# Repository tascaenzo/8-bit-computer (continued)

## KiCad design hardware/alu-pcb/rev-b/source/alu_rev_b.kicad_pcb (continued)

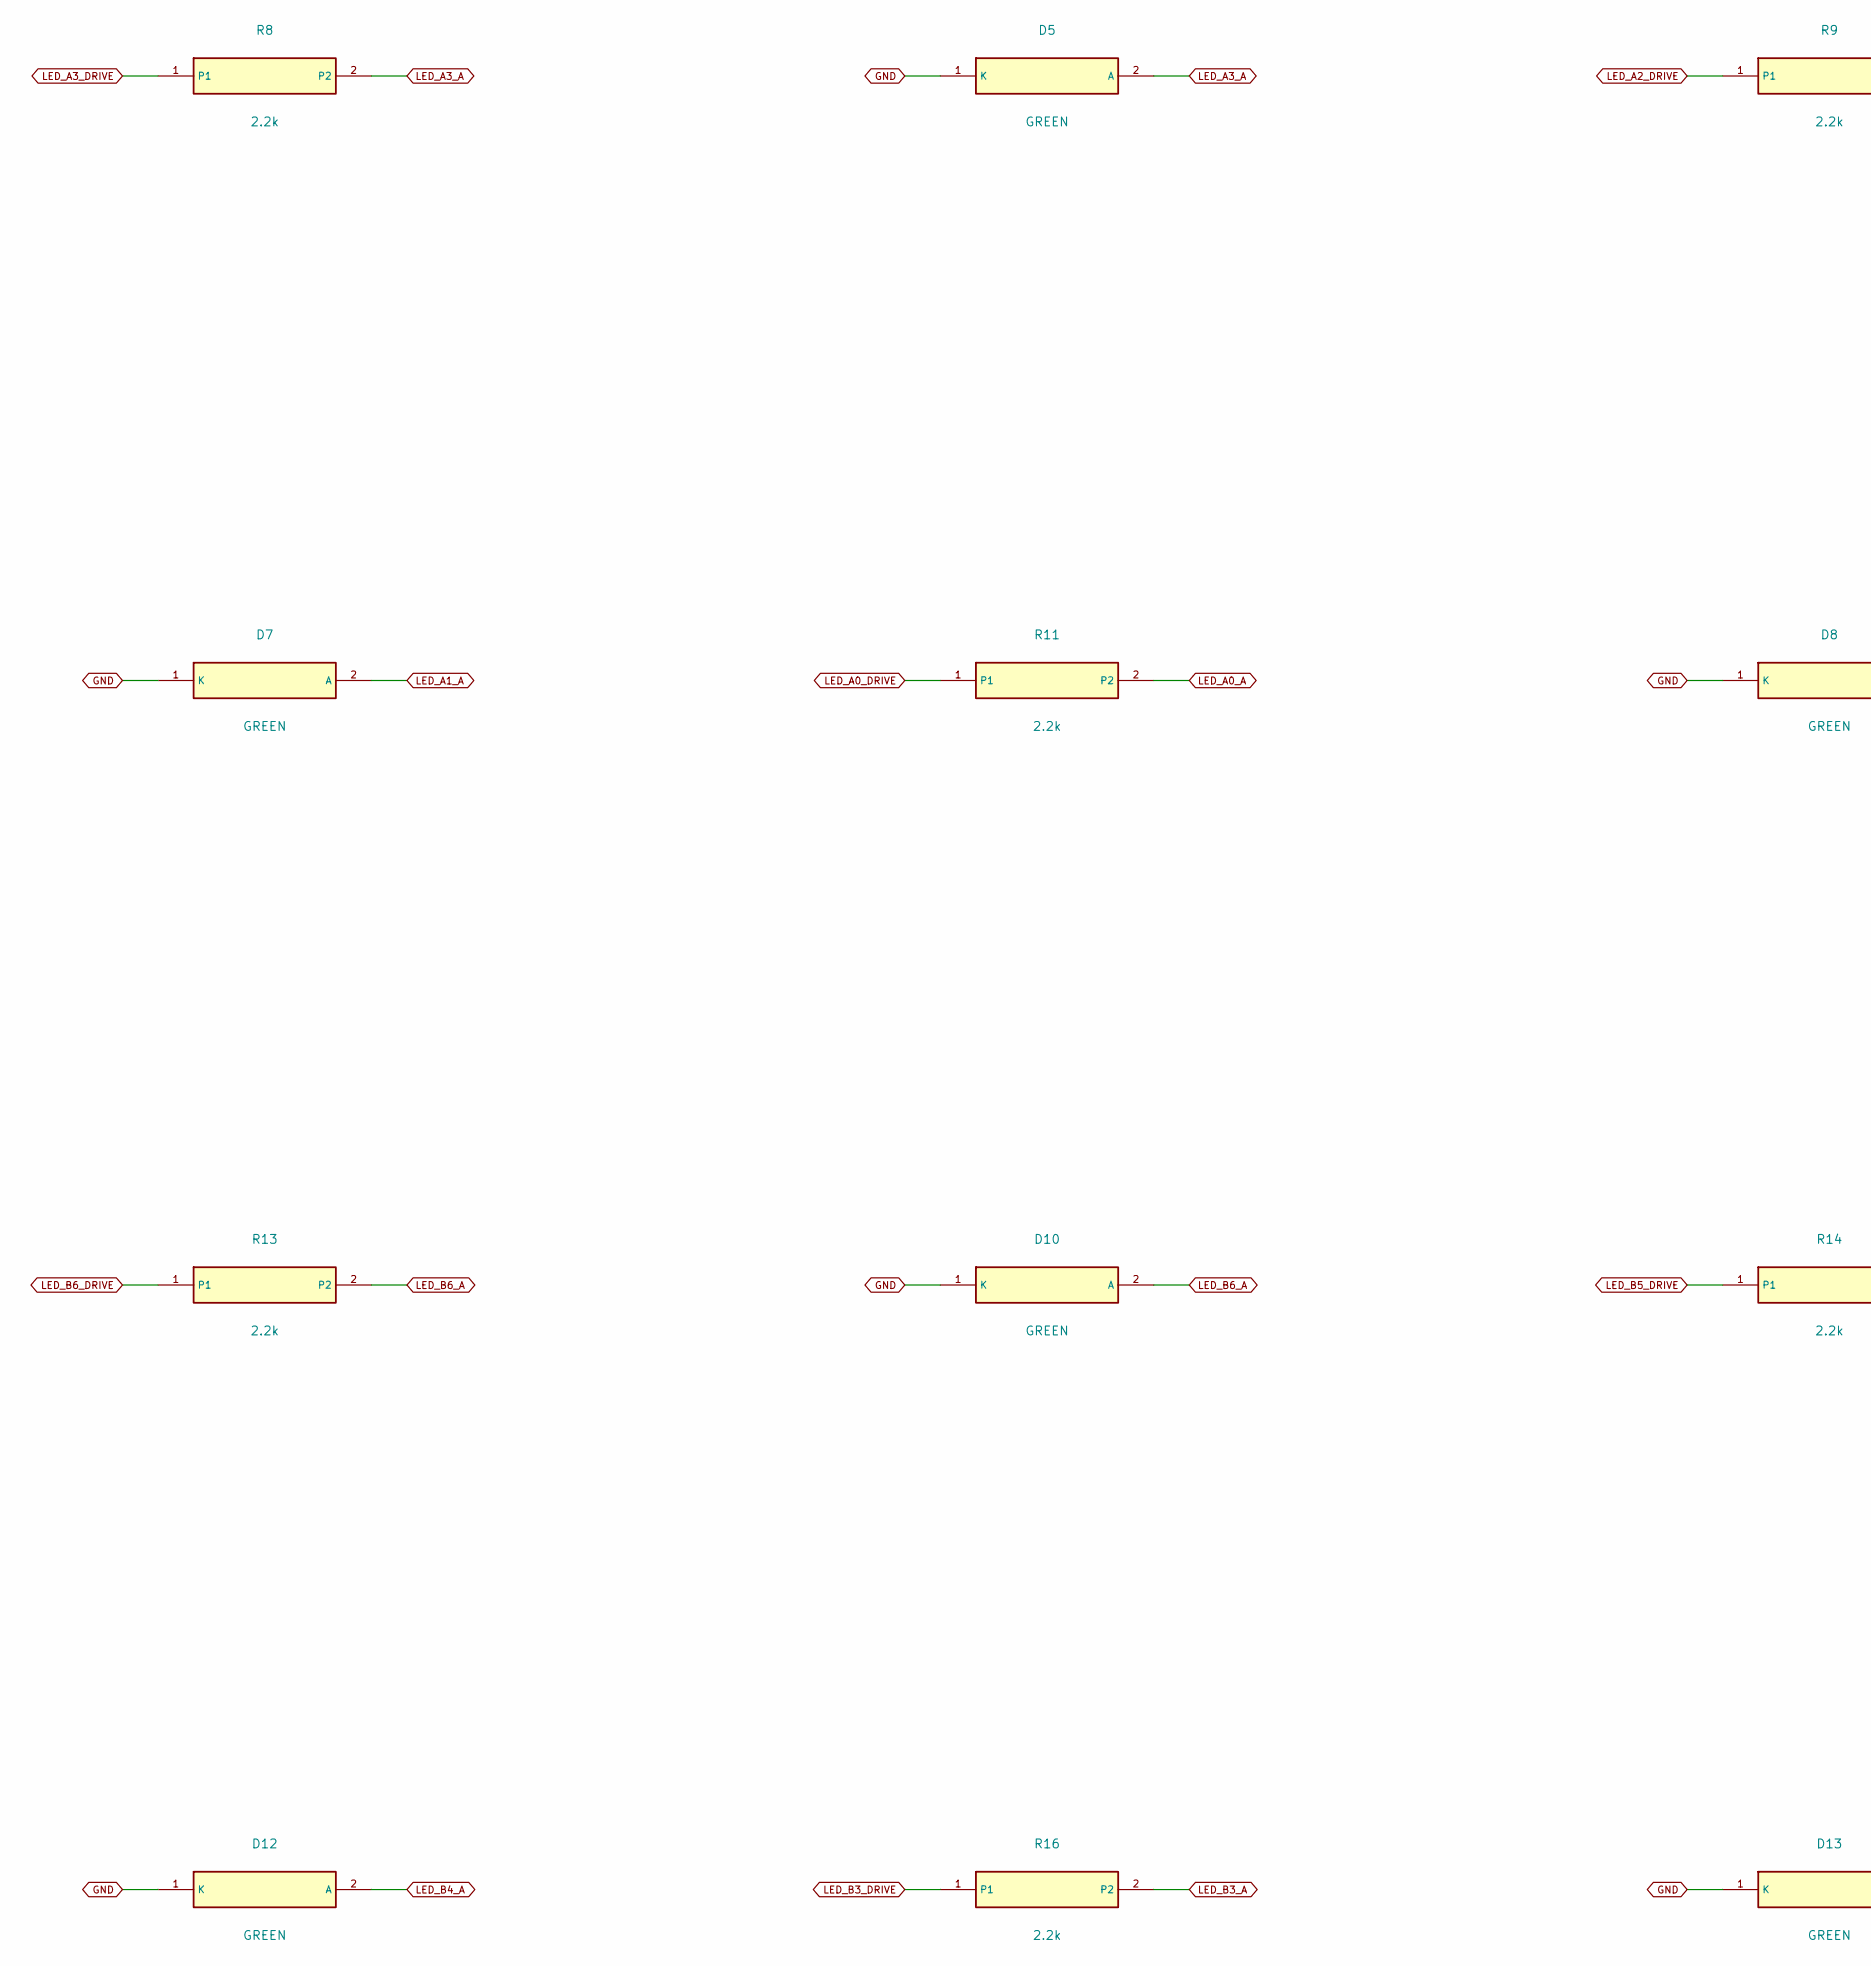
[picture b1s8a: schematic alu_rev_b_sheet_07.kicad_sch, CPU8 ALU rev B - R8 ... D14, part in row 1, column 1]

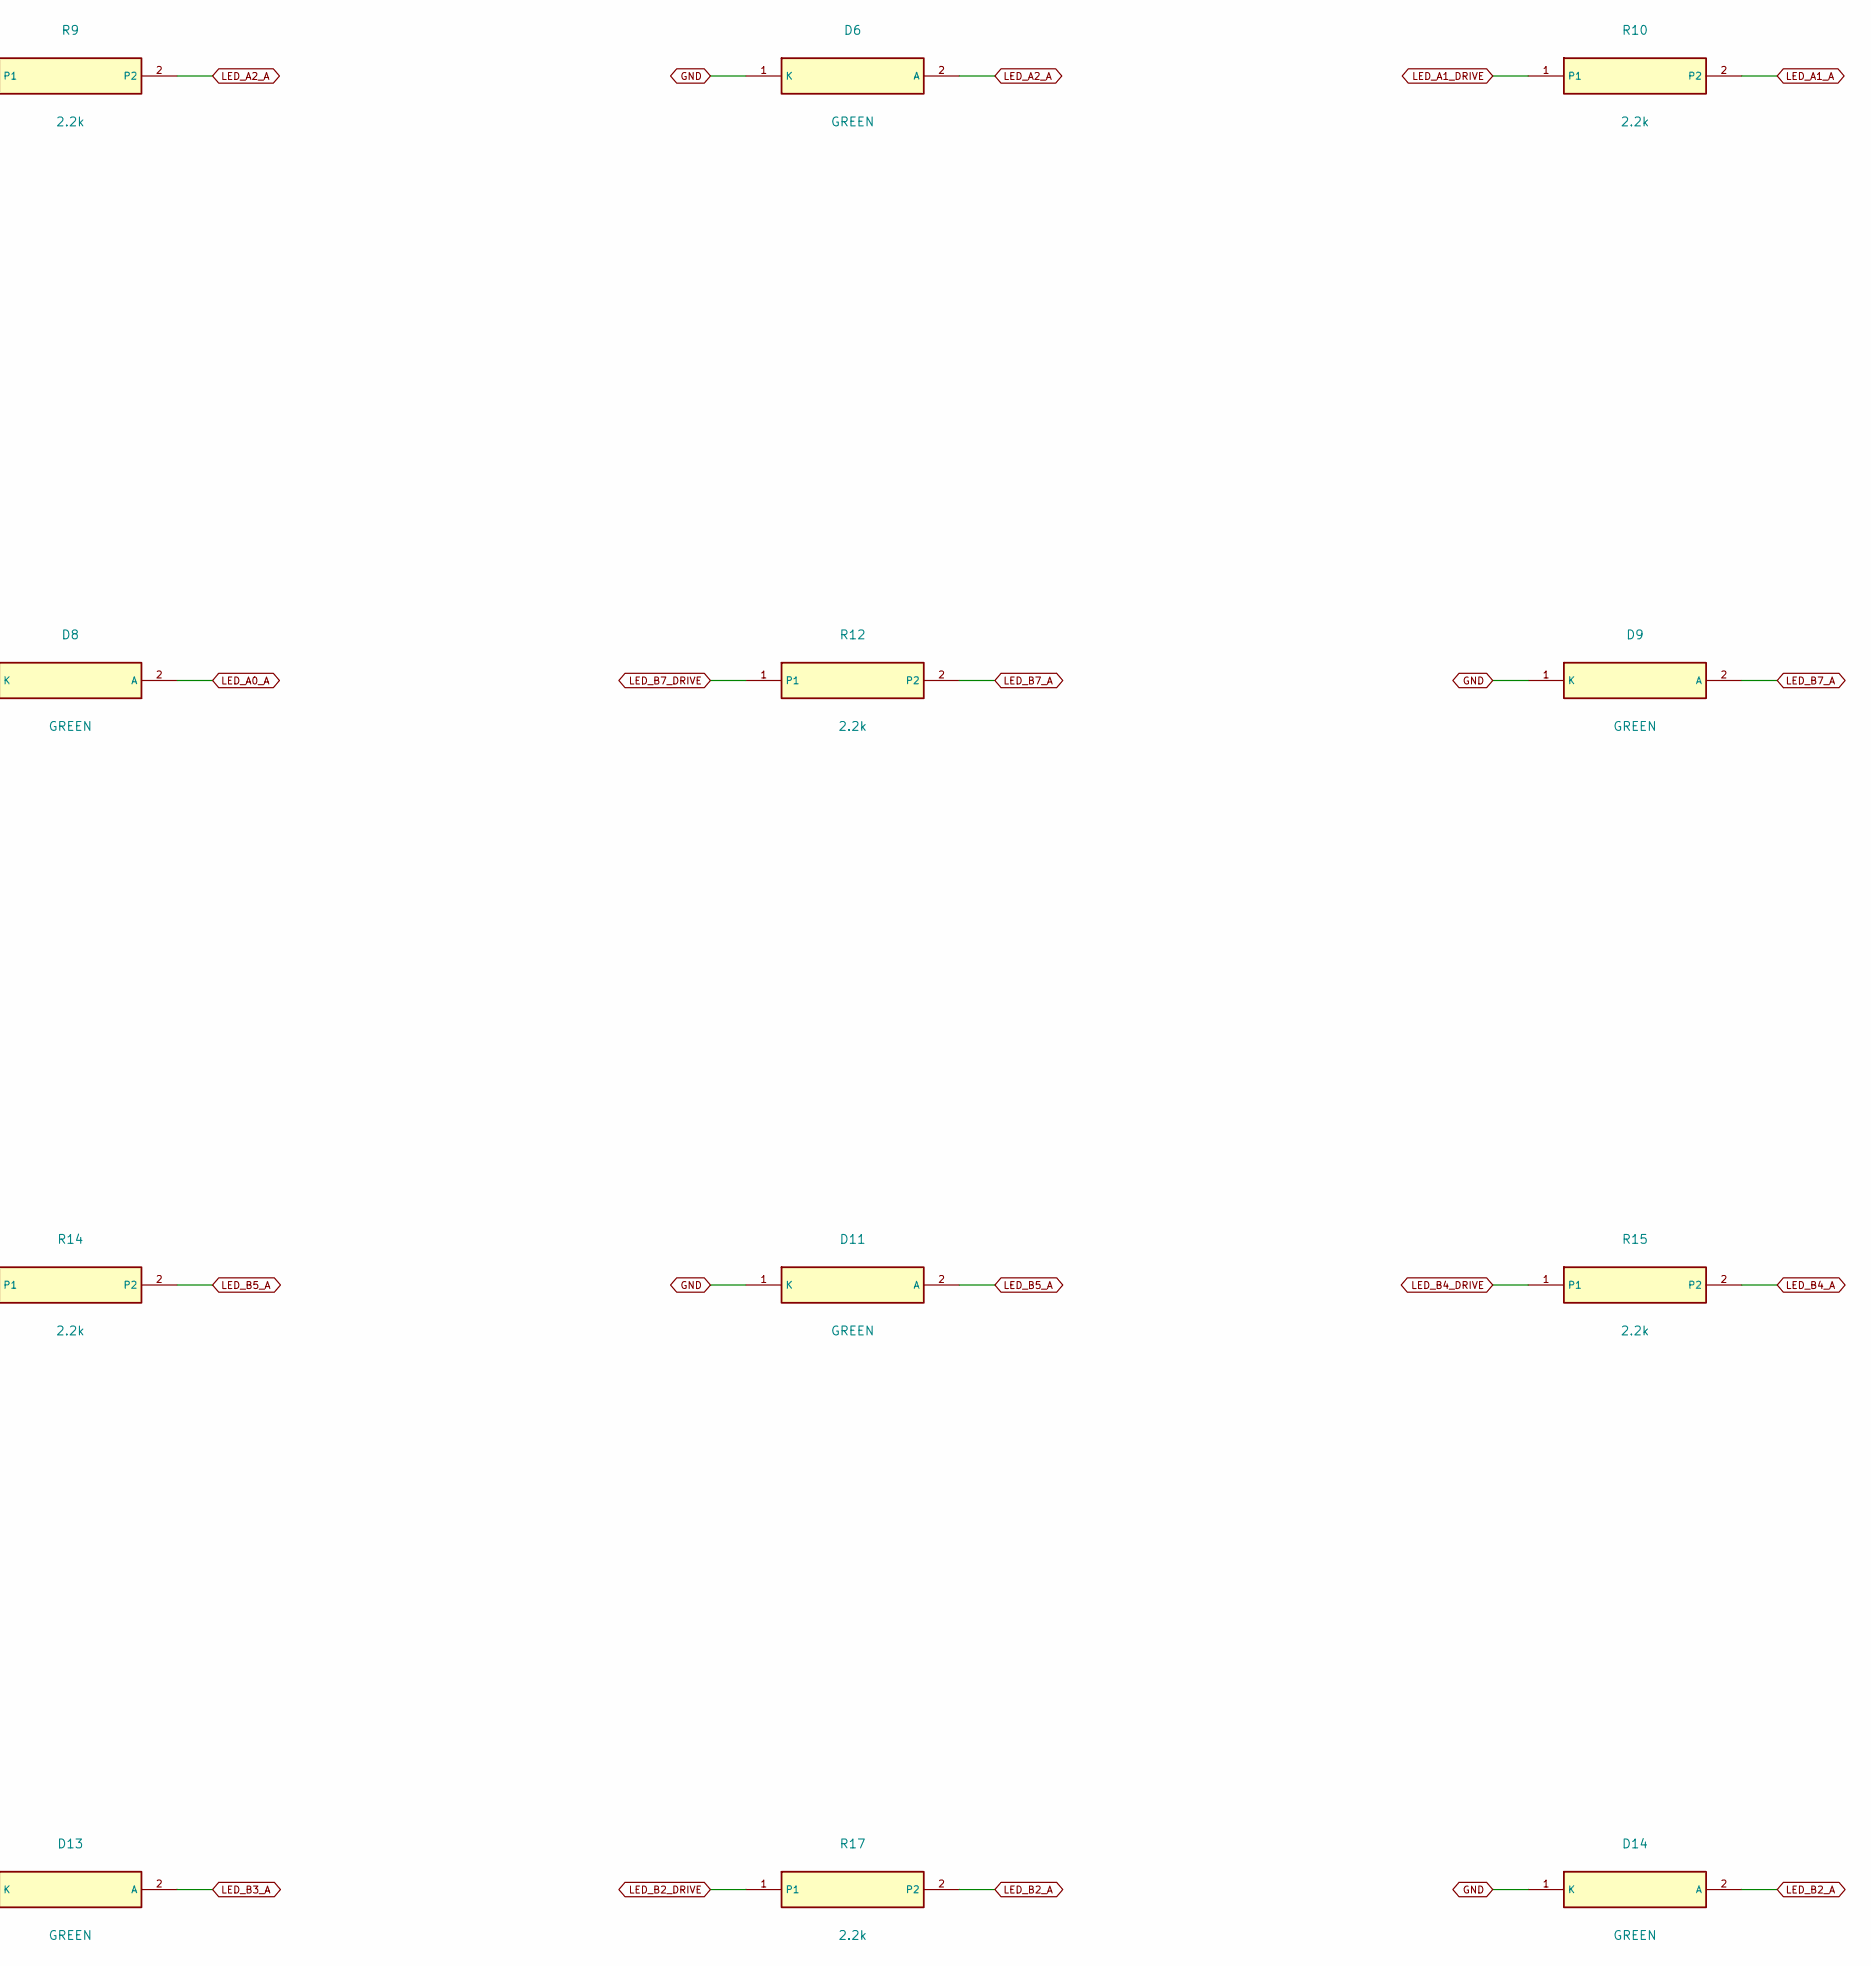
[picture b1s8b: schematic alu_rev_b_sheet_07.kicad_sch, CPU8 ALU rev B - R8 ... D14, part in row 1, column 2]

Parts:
D5, D6, D7, D8, D9, D10, D11, D12, D13, D14: GREEN; LED_D3.0mm_P2.54mm
R8, R9, R10, R11, R12, R13, R14, R15, R16, R17: 2.2k; R_Axial_P7.62mm

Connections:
GND: D5.1 (K), D6.1 (K), D7.1 (K), D8.1 (K), D9.1 (K), D10.1 (K), D11.1 (K), D12.1 (K), D13.1 (K), D14.1 (K); also elsewhere on the board
LED_A0_A: D8.2 (A), R11.2
LED_A0_DRIVE: R11.1; also elsewhere on the board
LED_A1_A: D7.2 (A), R10.2
LED_A1_DRIVE: R10.1; also elsewhere on the board
LED_A2_A: D6.2 (A), R9.2
LED_A2_DRIVE: R9.1; also elsewhere on the board
LED_A3_A: D5.2 (A), R8.2
LED_A3_DRIVE: R8.1; also elsewhere on the board
LED_B2_A: D14.2 (A), R17.2
LED_B2_DRIVE: R17.1; also elsewhere on the board
LED_B3_A: D13.2 (A), R16.2
LED_B3_DRIVE: R16.1; also elsewhere on the board
LED_B4_A: D12.2 (A), R15.2
LED_B4_DRIVE: R15.1; also elsewhere on the board
LED_B5_A: D11.2 (A), R14.2
LED_B5_DRIVE: R14.1; also elsewhere on the board
LED_B6_A: D10.2 (A), R13.2
LED_B6_DRIVE: R13.1; also elsewhere on the board
LED_B7_A: D9.2 (A), R12.2
LED_B7_DRIVE: R12.1; also elsewhere on the board

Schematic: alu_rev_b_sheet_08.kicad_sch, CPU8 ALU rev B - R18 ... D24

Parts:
D15, D16: GREEN; LED_D3.0mm_P2.54mm
D17, D18, D19, D20: YELLOW; LED_D3.0mm_P2.54mm
D21, D22, D23, D24: BLUE; LED_D3.0mm_P2.54mm
R18, R19, R20, R21, R22, R23, R24, R25, R26, R27: 2.2k; R_Axial_P7.62mm

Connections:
+5V: R24.1, R25.1, R26.1, R27.1; also elsewhere on the board
GND: D15.1 (K), D16.1 (K), D17.1 (K), D18.1 (K), D19.1 (K), D20.1 (K); also elsewhere on the board
LED_AND_A: D21.2 (A), R24.2
LED_B0_A: D16.2 (A), R19.2
LED_B0_DRIVE: R19.1; also elsewhere on the board
LED_B1_A: D15.2 (A), R18.2
LED_B1_DRIVE: R18.1; also elsewhere on the board
LED_C_A: D17.2 (A), R20.2
LED_C_DRIVE: R20.1; also elsewhere on the board
LED_NOR_A: D24.2 (A), R27.2
LED_N_A: D19.2 (A), R22.2
LED_N_DRIVE: R22.1; also elsewhere on the board
LED_OR_A: D22.2 (A), R25.2
LED_O_A: D20.2 (A), R23.2
LED_O_DRIVE: R23.1; also elsewhere on the board
LED_XOR_A: D23.2 (A), R26.2
LED_Z_A: D18.2 (A), R21.2
LED_Z_DRIVE: R21.1; also elsewhere on the board
OP_AND_n: D21.1 (K); also elsewhere on the board
OP_NOR_n: D24.1 (K); also elsewhere on the board
OP_OR_n: D22.1 (K); also elsewhere on the board
OP_XOR_n: D23.1 (K); also elsewhere on the board

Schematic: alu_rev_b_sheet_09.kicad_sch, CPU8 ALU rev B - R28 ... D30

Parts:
D25, D26, D27, D28, D29, D30: BLUE; LED_D3.0mm_P2.54mm
R28, R29, R30, R31, R32, R33: 2.2k; R_Axial_P7.62mm

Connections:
+5V: R28.1, R29.1, R30.1, R31.1, R32.1, R33.1; also elsewhere on the board
LED_ADD_A: D28.2 (A), R31.2
LED_CMP_A: D30.2 (A), R33.2
LED_NAND_A: D25.2 (A), R28.2
LED_NOT_A: D27.2 (A), R30.2
LED_SUB_A: D29.2 (A), R32.2
LED_XNOR_A: D26.2 (A), R29.2
OP_ADD_n: D28.1 (K); also elsewhere on the board
OP_CMP_n: D30.1 (K); also elsewhere on the board
OP_NAND_n: D25.1 (K); also elsewhere on the board
OP_NOT_n: D27.1 (K); also elsewhere on the board
OP_SUB_n: D29.1 (K); also elsewhere on the board
OP_XNOR_n: D26.1 (K); also elsewhere on the board

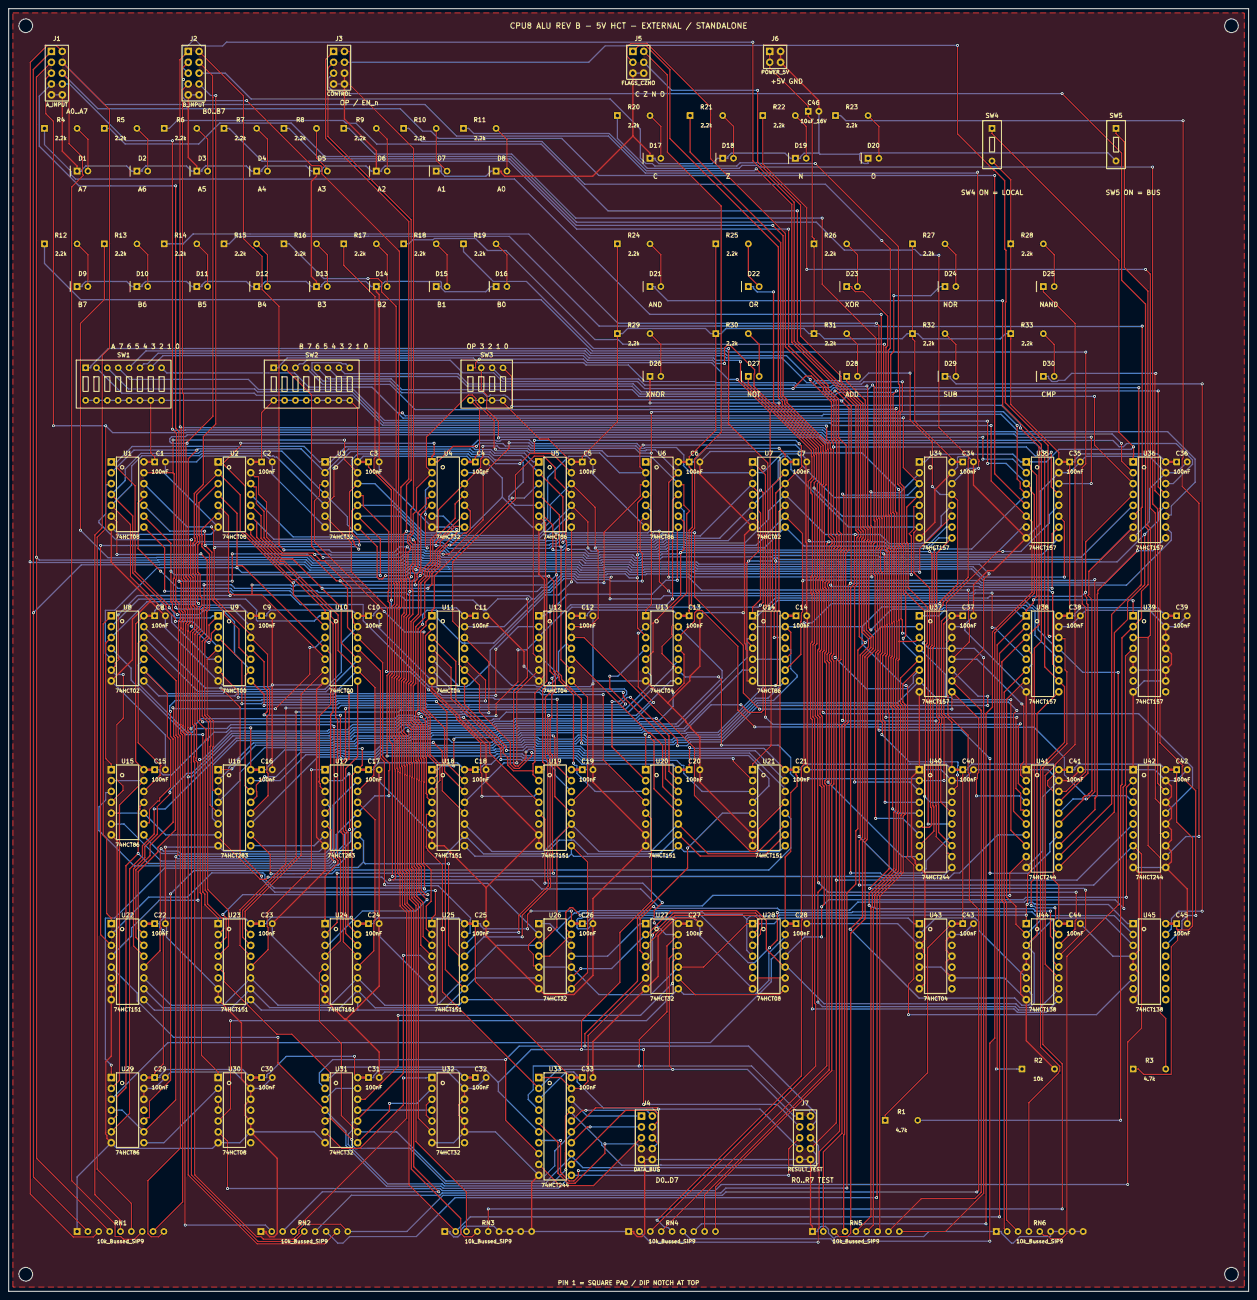
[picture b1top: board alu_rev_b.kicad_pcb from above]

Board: 2 copper layers, 290.0 x 300.0 mm, 172 parts (0 on the bottom side), 242 nets.

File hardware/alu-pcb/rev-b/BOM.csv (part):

Reference,Value,Footprint,Purpose,Part_or_requirement,Mounting_specification
U1,74HCT08,DIP-14_W7.62mm,AND,74HCT08 compatible pinout,5V HCT; PDIP-14; rows 7.62mm; optional socket
U2,74HCT08,DIP-14_W7.62mm,AND,74HCT08 compatible pinout,5V HCT; PDIP-14; rows 7.62mm; optional socket
U3,74HCT32,DIP-14_W7.62mm,OR,74HCT32 compatible pinout,5V HCT; PDIP-14; rows 7.62mm; optional socket
U4,74HCT32,DIP-14_W7.62mm,OR,74HCT32 compatible pinout,5V HCT; PDIP-14; rows 7.62mm; optional socket
U5,74HCT86,DIP-14_W7.62mm,XOR,74HCT86 compatible pinout,5V HCT; PDIP-14; rows 7.62mm; optional socket
U6,74HCT86,DIP-14_W7.62mm,XOR,74HCT86 compatible pinout,5V HCT; PDIP-14; rows 7.62mm; optional socket
U7,74HCT02,DIP-14_W7.62mm,NOR,74HCT02 compatible pinout,5V HCT; PDIP-14; rows 7.62mm; optional socket
U8,74HCT02,DIP-14_W7.62mm,NOR,74HCT02 compatible pinout,5V HCT; PDIP-14; rows 7.62mm; optional socket
U9,74HCT00,DIP-14_W7.62mm,NAND,74HCT00 compatible pinout,5V HCT; PDIP-14; rows 7.62mm; optional socket
U10,74HCT00,DIP-14_W7.62mm,NAND,74HCT00 compatible pinout,5V HCT; PDIP-14; rows 7.62mm; optional socket
U11,74HCT04,DIP-14_W7.62mm,XNOR / NOT,74HCT04 compatible pinout,5V HCT; PDIP-14; rows 7.62mm; optional socket
U12,74HCT04,DIP-14_W7.62mm,XNOR / NOT,74HCT04 compatible pinout,5V HCT; PDIP-14; rows 7.62mm; optional socket
U13,74HCT04,DIP-14_W7.62mm,XNOR / NOT,74HCT04 compatible pinout,5V HCT; PDIP-14; rows 7.62mm; optional socket
U14,74HCT86,DIP-14_W7.62mm,B complement,74HCT86 compatible pinout,5V HCT; PDIP-14; rows 7.62mm; optional socket
U15,74HCT86,DIP-14_W7.62mm,B complement,74HCT86 compatible pinout,5V HCT; PDIP-14; rows 7.62mm; optional socket
U16,74HCT283,DIP-16_W7.62mm,Adder bits 0..3,CD74HCT283E,5V HCT; PDIP-16; rows 7.62mm; optional socket
U17,74HCT283,DIP-16_W7.62mm,Adder bits 4..7,CD74HCT283E,5V HCT; PDIP-16; rows 7.62mm; optional socket
U18,74HCT151,DIP-16_W7.62mm,Result select bit 0,CD74HCT151E,5V HCT; PDIP-16; rows 7.62mm; optional socket
U19,74HCT151,DIP-16_W7.62mm,Result select bit 1,CD74HCT151E,5V HCT; PDIP-16; rows 7.62mm; optional socket
U20,74HCT151,DIP-16_W7.62mm,Result select bit 2,CD74HCT151E,5V HCT; PDIP-16; rows 7.62mm; optional socket
U21,74HCT151,DIP-16_W7.62mm,Result select bit 3,CD74HCT151E,5V HCT; PDIP-16; rows 7.62mm; optional socket
U22,74HCT151,DIP-16_W7.62mm,Result select bit 4,CD74HCT151E,5V HCT; PDIP-16; rows 7.62mm; optional socket
U23,74HCT151,DIP-16_W7.62mm,Result select bit 5,CD74HCT151E,5V HCT; PDIP-16; rows 7.62mm; optional socket
U24,74HCT151,DIP-16_W7.62mm,Result select bit 6,CD74HCT151E,5V HCT; PDIP-16; rows 7.62mm; optional socket
U25,74HCT151,DIP-16_W7.62mm,Result select bit 7,CD74HCT151E,5V HCT; PDIP-16; rows 7.62mm; optional socket
U26,74HCT32,DIP-14_W7.62mm,Opcode / output control,74HCT32 compatible pinout,5V HCT; PDIP-14; rows 7.62mm; optional socket
U27,74HCT32,DIP-14_W7.62mm,Opcode / output control,74HCT32 compatible pinout,5V HCT; PDIP-14; rows 7.62mm; optional socket
U28,74HCT08,DIP-14_W7.62mm,Opcode / output control,74HCT08 compatible pinout,5V HCT; PDIP-14; rows 7.62mm; optional socket
U29,74HCT86,DIP-14_W7.62mm,Carry / overflow,74HCT86 compatible pinout,5V HCT; PDIP-14; rows 7.62mm; optional socket
U30,74HCT08,DIP-14_W7.62mm,Carry / overflow,74HCT08 compatible pinout,5V HCT; PDIP-14; rows 7.62mm; optional socket
U31,74HCT32,DIP-14_W7.62mm,Zero flag,74HCT32 compatible pinout,5V HCT; PDIP-14; rows 7.62mm; optional socket
U32,74HCT32,DIP-14_W7.62mm,Zero flag,74HCT32 compatible pinout,5V HCT; PDIP-14; rows 7.62mm; optional socket
U33,74HCT244,DIP-20_W7.62mm,Shared bus output,SN74HCT244N,5V HCT; PDIP-20; rows 7.62mm; optional socket
U34,74HCT157,DIP-16_W7.62mm,External / standalone input selection,SN74HCT157N,5V HCT; PDIP-16; rows 7.62mm; optional socket
U35,74HCT157,DIP-16_W7.62mm,External / standalone input selection,SN74HCT157N,5V HCT; PDIP-16; rows 7.62mm; optional socket
U36,74HCT157,DIP-16_W7.62mm,External / standalone input selection,SN74HCT157N,5V HCT; PDIP-16; rows 7.62mm; optional socket
U37,74HCT157,DIP-16_W7.62mm,External / standalone input selection,SN74HCT157N,5V HCT; PDIP-16; rows 7.62mm; optional socket
U38,74HCT157,DIP-16_W7.62mm,External / standalone input selection,SN74HCT157N,5V HCT; PDIP-16; rows 7.62mm; optional socket
U39,74HCT157,DIP-16_W7.62mm,External / standalone input selection,SN74HCT157N,5V HCT; PDIP-16; rows 7.62mm; optional socket
U40,74HCT244,DIP-20_W7.62mm,Operand / flag LED driver,SN74HCT244N,5V HCT; PDIP-20; rows 7.62mm; optional socket
U41,74HCT244,DIP-20_W7.62mm,Operand / flag LED driver,SN74HCT244N,5V HCT; PDIP-20; rows 7.62mm; optional socket
U42,74HCT244,DIP-20_W7.62mm,Operand / flag LED driver,SN74HCT244N,5V HCT; PDIP-20; rows 7.62mm; optional socket
U43,74HCT04,DIP-14_W7.62mm,Opcode LED decoder enable,74HCT04 compatible pinout,5V HCT; PDIP-14; rows 7.62mm; optional socket
U44,74HCT138,DIP-16_W7.62mm,Operation LED decoder,SN74HCT138N,5V HCT; PDIP-16; rows 7.62mm; optional socket
U45,74HCT138,DIP-16_W7.62mm,Operation LED decoder,SN74HCT138N,5V HCT; PDIP-16; rows 7.62mm; optional socket
C1,100nF,C_Disc_P2.50mm,Local bypass,100nF 25V ceramic,Pitch 2.50mm; body max 4x3mm; nonpolarized
C2,100nF,C_Disc_P2.50mm,Local bypass,100nF 25V ceramic,Pitch 2.50mm; body max 4x3mm; nonpolarized
C3,100nF,C_Disc_P2.50mm,Local bypass,100nF 25V ceramic,Pitch 2.50mm; body max 4x3mm; nonpolarized
C4,100nF,C_Disc_P2.50mm,Local bypass,100nF 25V ceramic,Pitch 2.50mm; body max 4x3mm; nonpolarized
C5,100nF,C_Disc_P2.50mm,Local bypass,100nF 25V ceramic,Pitch 2.50mm; body max 4x3mm; nonpolarized
C6,100nF,C_Disc_P2.50mm,Local bypass,100nF 25V ceramic,Pitch 2.50mm; body max 4x3mm; nonpolarized
C7,100nF,C_Disc_P2.50mm,Local bypass,100nF 25V ceramic,Pitch 2.50mm; body max 4x3mm; nonpolarized
C8,100nF,C_Disc_P2.50mm,Local bypass,100nF 25V ceramic,Pitch 2.50mm; body max 4x3mm; nonpolarized
C9,100nF,C_Disc_P2.50mm,Local bypass,100nF 25V ceramic,Pitch 2.50mm; body max 4x3mm; nonpolarized
C10,100nF,C_Disc_P2.50mm,Local bypass,100nF 25V ceramic,Pitch 2.50mm; body max 4x3mm; nonpolarized
C11,100nF,C_Disc_P2.50mm,Local bypass,100nF 25V ceramic,Pitch 2.50mm; body max 4x3mm; nonpolarized
C12,100nF,C_Disc_P2.50mm,Local bypass,100nF 25V ceramic,Pitch 2.50mm; body max 4x3mm; nonpolarized
C13,100nF,C_Disc_P2.50mm,Local bypass,100nF 25V ceramic,Pitch 2.50mm; body max 4x3mm; nonpolarized
C14,100nF,C_Disc_P2.50mm,Local bypass,100nF 25V ceramic,Pitch 2.50mm; body max 4x3mm; nonpolarized
C15,100nF,C_Disc_P2.50mm,Local bypass,100nF 25V ceramic,Pitch 2.50mm; body max 4x3mm; nonpolarized
C16,100nF,C_Disc_P2.50mm,Local bypass,100nF 25V ceramic,Pitch 2.50mm; body max 4x3mm; nonpolarized
C17,100nF,C_Disc_P2.50mm,Local bypass,100nF 25V ceramic,Pitch 2.50mm; body max 4x3mm; nonpolarized
C18,100nF,C_Disc_P2.50mm,Local bypass,100nF 25V ceramic,Pitch 2.50mm; body max 4x3mm; nonpolarized
C19,100nF,C_Disc_P2.50mm,Local bypass,100nF 25V ceramic,Pitch 2.50mm; body max 4x3mm; nonpolarized
C20,100nF,C_Disc_P2.50mm,Local bypass,100nF 25V ceramic,Pitch 2.50mm; body max 4x3mm; nonpolarized
C21,100nF,C_Disc_P2.50mm,Local bypass,100nF 25V ceramic,Pitch 2.50mm; body max 4x3mm; nonpolarized
C22,100nF,C_Disc_P2.50mm,Local bypass,100nF 25V ceramic,Pitch 2.50mm; body max 4x3mm; nonpolarized
C23,100nF,C_Disc_P2.50mm,Local bypass,100nF 25V ceramic,Pitch 2.50mm; body max 4x3mm; nonpolarized
C24,100nF,C_Disc_P2.50mm,Local bypass,100nF 25V ceramic,Pitch 2.50mm; body max 4x3mm; nonpolarized
C25,100nF,C_Disc_P2.50mm,Local bypass,100nF 25V ceramic,Pitch 2.50mm; body max 4x3mm; nonpolarized
C26,100nF,C_Disc_P2.50mm,Local bypass,100nF 25V ceramic,Pitch 2.50mm; body max 4x3mm; nonpolarized
C27,100nF,C_Disc_P2.50mm,Local bypass,100nF 25V ceramic,Pitch 2.50mm; body max 4x3mm; nonpolarized
C28,100nF,C_Disc_P2.50mm,Local bypass,100nF 25V ceramic,Pitch 2.50mm; body max 4x3mm; nonpolarized
C29,100nF,C_Disc_P2.50mm,Local bypass,100nF 25V ceramic,Pitch 2.50mm; body max 4x3mm; nonpolarized
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
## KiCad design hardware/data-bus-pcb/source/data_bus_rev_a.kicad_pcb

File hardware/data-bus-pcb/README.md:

# CPU8 — bus dati a 8 bit, revisione A

Layout slim con LED compatti e switch del 7 ottobre 2026: **235 × 40 mm**, rispetto ai precedenti 180 × 60 mm.
Il 74HCT244 segue la fila degli otto connettori sul lato destro.
Serigrafia sul fronte: **Progettato da Enzo Tasca**. Questa versione usa la
revisione **A**, come richiesto, e sostituisce il precedente layout B.
Le piedinature elettriche rimangono compatibili con ALU J4/J6.

PCB da saldare con **otto porte bidirezionali** J1…J8, **otto LED D7…D0**,
un buffer per gli indicatori e una spia PWR. Tutte le porte sono collegate
in parallelo: qualunque porta può essere usata da un modulo che legge
oppure da un modulo che scrive. Il connettore dati è compatibile con
**J4 dell'ALU revisione A** del repository.

La scheda distribuisce dati e massa. L'alimentazione del monitor entra da
J9; il clock, i comandi LOAD e le abilitazioni delle uscite viaggiano
separatamente, dalla centralina ai rispettivi moduli.

## File consegnati

- `CPU8_DATA_BUS_REV_A_GERBER.zip`: da caricare sul servizio di produzione PCB.
- `CPU8_DATA_BUS_REV_A_PROJECT.zip`: sorgenti KiCad, librerie, schema, BOM e rapporti.
- `source/data_bus_rev_a.kicad_pro`: progetto da aprire in KiCad.
- `data_bus_rev_a_schematic.pdf`: schema elettrico, tre pagine.
- `data_bus_rev_a_preview.png`: anteprima della scheda nuda, senza modelli dei componenti.
- `data_bus_rev_a_layout.svg`: piste e serigrafia.
- `BOM.csv`: distinta con valori, package e dimensioni per il montaggio.
- `verification/`: controlli elettrici, di layout, di collegamento e integrità degli export.

Lo ZIP Gerber ordina una **scheda vuota**: i componenti e gli zoccoli vanno
acquistati e saldati separatamente. Non è stato effettuato alcun ordine.

## Piedinatura

Guardando il lato componenti con il titolo in alto, il pin 1 è la piazzola
quadrata in alto a sinistra. Tutti i connettori hanno due colonne a passo
2,54 mm: righe 1/2, 3/4, 5/6, ecc.

| Porta dati J1…J8 | Colonna sinistra | Colonna destra |
| --- | --- | --- |
| Riga 1 | Pin 1: D0 | Pin 2: D1 |
| Riga 2 | Pin 3: D2 | Pin 4: D3 |
| Riga 3 | Pin 5: D4 | Pin 6: D5 |
| Riga 4 | Pin 7: D6 | Pin 8: D7 |
| Riga 5 | Pin 9: GND | Pin 10: GND |

**Le porte dati non contengono +5 V.** Usare header maschi non schermati
2×5 e cavi con collegamento pin-a-pin. Non ruotare il connettore di 180°;
controllare i cavi con il tester prima dell'accensione.

| J9 POWER_5V | Colonna sinistra | Colonna destra |
| --- | --- | --- |
| Riga 1 | Pin 1: +5 V | Pin 2: GND |
| Riga 2 | Pin 3: +5 V | Pin 4: GND |

J9 è un header 2×2 con la stessa piedinatura di J6 dell'ALU. Alimentare
monitor e moduli da una sorgente comune a **5 V regolati** e collegare le
masse. I moduli ricevono +5 V dai loro connettori di alimentazione, non
attraverso J1…J8. I pin duplicati di J9 sono la stessa rete, non due ingressi
di alimentazione indipendenti.

## Come si legge e si scrive sul bus

**Lettura:** collegare gli ingressi dati di un registro o di un altro
circuito a una porta. Quel modulo acquisisce il dato quando riceve il suo
clock/comando LOAD. Il bus non genera questi comandi.

**Scrittura:** collegare le uscite di un buffer tri-state del modulo a una
porta. La centralina abilita quel buffer quando il modulo deve trasmettere
il dato; lo disabilita negli altri momenti. Esempi sono un registro con
buffer 74HCT244/245, l'uscita della RAM opportunamente controllata o J4
dell'ALU. **Può essere abilitato un solo modulo che scrive alla volta**;
più moduli possono leggere contemporaneamente.

Non collegare direttamente sul bus uscite push-pull sempre attive di
registri o porte logiche. Questa scheda non contiene un arbitro e non
rileva due moduli che pilotano il bus contemporaneamente. Anche se i LED
mostrano un valore, non significa che le abilitazioni siano corrette.

Il monitor U1 è un [SN74HCT244N](https://www.ti.com/lit/ds/symlink/sn74hct244.pdf):
i suoi ingressi leggono il bus, le sue uscite alimentano soltanto i LED.
Il carico dei LED è quindi separato dalle linee dati. Le due abilitazioni
del monitor, pin 1 e 19, sono collegate alla rete `LED_OE_n`: **SW1 ON**
le porta a GND e abilita gli indicatori; **SW1 OFF** le lascia alte tramite
R10 da 10 kΩ e disabilita le uscite LED. Nessuna uscita attiva del monitor pilota D0…D7.

RN1 aggiunge un pull-down da 10 kΩ per bit, con carico nominale di 0,5 mA
quando un bit è a 5 V. Con questa scheda da sola e senza un trasmettitore,
i LED dati sono spenti. Gli indicatori non distinguono uno zero trasmesso
da un bus non pilotato. Con moduli esterni, verificare il carico totale e
le tensioni effettive del bus durante il collaudo.

I LED visualizzano il valore istantaneo e non lo memorizzano: sono utili
con dati statici e clock manuale. A velocità elevate l'occhio vede una
luminosità media; per catturare un byte a un preciso istante occorre un
registro o un analizzatore logico. La scheda non include un latch del display.

Gli ingressi del monitor accettano livelli TTL. Il bus resta un'interfaccia
logica a 5 V: per FPGA e altri dispositivi a 3,3 V usare adattamento dei
livelli adeguato ai dispositivi effettivi. Nessuna frequenza massima è
stata misurata. Per iniziare usare pochi moduli e cavi corti.

## Collegamento all'ALU esistente

1. Collegare **ALU J4 → BUS J1**, pin-a-pin. J2…J8 restano disponibili.
2. Alimentare **ALU J6** e **BUS J9** con la stessa sorgente a 5 V e GND.
3. Sul bus mettere **SW1 ON** per accendere gli indicatori. Sull'ALU mettere SW4 ON per gli operandi locali, inizialmente SW5 OFF.
4. Impostare A = `00000101`, B = `00000011`, OP = `0111` (ADD).
5. Abilitare l'ALU con SW5 ON: 5 + 3 = 8, quindi si accende **D3** sul bus.
6. Disabilitare l'ALU prima di abilitare un altro modulo che scrive.

Gli ingressi A/B dell'ALU, J1/J2, normalmente ricevono i valori dai
registri A e B: **non sono le porte per l'uscita dell'ALU sul bus**.
J7 dell'ALU è un'uscita del risultato interno sempre attiva: non usarla
come porta bus al posto di J4.

Con un registro collegato, il percorso è:

```text
ALU J4 ── BUS J1 ── linee D0…D7 comuni ── BUS J2 ── ingressi del registro
                     │
                     └── U1 ── resistori ── LED D7…D0
```

Per far leggere quel byte al registro, la centralina deve inviare al
registro il suo comando di acquisizione. Per farlo scrivere in un altro
momento, serve un'uscita tri-state del registro controllata separatamente.

## LED ravvicinati e interruttore SW1

I LED hanno un interasse di **4 mm**, con **2 mm aggiuntivi ogni quattro bit**:
D7 D6 D5 D4 | D3 D2 D1 D0.
I LED dati/indirizzo hanno i piedini disposti verticalmente, distanti 2,54 mm:
**pin 1 catodo in alto, pin 2 anodo in basso**. PWR mantiene i piedini
orizzontali con catodo a sinistra. Le piazzole quadrate identificano il pin 1.

**SW1 = C&K SDA01H0BD**, SPST a una posizione, through-hole, file distanti
7,62 mm; pin 1 = `LED_OE_n`, pin 2 = GND. **ON chiude il contatto**.
R10 è un resistore assiale **10 kΩ**, 1/4 W, passo 7,62 mm, tra +5 V e OE_n.
Un solo switch governa tutti i buffer LED di questa scheda.

- **ON:** OE_n basso; i LED mostrano i bit del bus.
- **OFF:** OE_n alto; le uscite dei 74HCT244 sono in alta impedenza e i LED
  dei bit sono inattivi. La spia PWR resta accesa.
- L'interruttore non interrompe dati, indirizzi o alimentazione degli altri
  moduli; i pull-down del bus restano presenti. Non è un interruttore generale.

Il livello alto/basso e lo stato tri-state seguono il
[datasheet TI SN74HCT244](https://www.ti.com/lit/ds/symlink/sn74hct244.pdf).
Ingombro e piedinatura di SW1 seguono il
[datasheet C&K SDA](https://www.ckswitches.com/media/1327/sda.pdf).

## Componenti e montaggio

33 componenti: un SN74HCT244N, otto connettori 2×5, un connettore 2×2,
nove LED verdi da 3 mm, nove resistori da 2,2 kΩ, una rete resistiva SIP-9,
un condensatore ceramico, un elettrolitico, SW1 e un pull-up da 10 kΩ. Aggiungere uno zoccolo DIP-20
con file distanti 7,62 mm. Tutti i componenti sono through-hole.

- **U1:** PDIP-20, tacca in alto e pin 1 quadrato. Non sostituire con SOIC.
- **D1…D8:** rispettivamente D0…D7; sul PCB la fila è ordinata da sinistra
  **D7, D6, D5, D4, D3, D2, D1, D0**. La sigla componente D8 identifica
  quindi il LED del bit D7: seguire il testo del bit sotto ciascun LED.
- **D9:** spia PWR. Tutti i LED hanno **pin 1 catodo**, **pin 2 anodo**;
  la linea piatta in serigrafia indica il catodo. Passo 2,54 mm.
- **R1…R9:** 2,2 kΩ, 1/4 W, passo 7,62 mm. Corrente LED nell'ordine
  di 1 mA; usare LED ad alta efficienza.
- **RN1:** rete **bussed SIP-9, otto resistenze da 10 kΩ**, comune al pin 1
  quadrato verso GND. Passo 2,54 mm. Una rete con resistenze isolate non
  è compatibile.
- **C1:** 100 nF ceramico, passo 2,50 mm, corpo entro 4 × 3 mm.
- **C2:** 10 µF, almeno 16 V, passo 2,50 mm, diametro entro 5 mm;
  **pin 1 positivo**, pin 2 GND. Il PCB riporta anche il simbolo +.
- I piani GND usano connessioni solide: saldare i pin di massa con una
  punta adeguata e sufficiente trasferimento di calore.

## Ordine PCB e verifiche

| Parametro | Valore |
| --- | --- |
| Dimensioni | **235 × 40 mm** |
| Rame | Due strati, 1 oz |
| Materiale / spessore | FR-4 / 1,6 mm |
| Maschera / serigrafia | Verde / bianca sul fronte |
| Finitura | HASL senza piombo o ENIG |
| Assemblaggio / stencil | Nessuno, montaggio manuale |
| Piste | 0,30 mm, restringimenti minimi 0,15 mm |
| Clearance | 0,25 mm; minimo assoluto di progetto 0,20 mm |
| Via | Diametro 0,70 mm, foro 0,30 mm |
| Fori componenti | 0,80 e 0,90 mm, metallizzati |
| Montaggio | Quattro fori 3,20 mm, non metallizzati |

Caricare il solo ZIP Gerber e controllare che l'anteprima del produttore
riconosca 235 × 40 mm, due strati di rame e i due file di foratura.

- ERC: **0 violazioni**.
- DRC: **0 violazioni**, **0 collegamenti mancanti**.
- Parità PCB/schema: **0 problemi**.
- Verifica di **512 casi**: 256 valori del bus × due stati di SW1; display
  corretto quando ON, uscite LED in alta impedenza quando OFF, porte bus invariate.
- Controllo dell'isolamento del monitor: nessuna sua uscita pilota il bus.
- Export KiCad 10.0.7, pacchetti con controllo d'integrità e manifest SHA-256.

**Il prototipo fisico non è ancora stato montato e collaudato.** Prima di
inserire U1 verificare polarità e alimentazione dello zoccolo. Accendere
inizialmente con alimentatore a corrente limitata e gli altri moduli
scollegati. Provare poi un solo trasmettitore, con dati statici, prima di
aggiungere registri e clock. Misurare livelli e tempi sotto carico prima
di aumentare la frequenza.

Gli script in `tools/` documentano costruzione e controlli. Il generatore
ricrea una scheda **senza piste** soltanto con `--rebuild-unrouted`;
per le normali modifiche aprire i sorgenti KiCad finali e preservare le piste.
La ricostruzione completa richiede nuovo export XML, `prepare_board.py`
con pcbnew, instradamento DSN/SES, `finish_board.py`, verifiche ed export.

## Disposizione meccanica del layout slim

- Quattro fori di montaggio da 3,2 mm: (4,4), (231,4), (4,36), (231,36) mm; origine nell'angolo superiore sinistro.
- J1…J8: pin 1 a x=10,33,56,79,102,125,148,171 mm, y=10 mm.
- U1: pin 1 a (195,10) mm; RN1 a destra dei connettori.
- LED da sinistra D7…D0, pin 1 a x=72,76,80,84,90,94,98,102 mm e y=30 mm; alimentazione J9 a destra.
- Componenti sempre sul fronte, integrati con tacca verso l'alto. I valori
  di header, rete resistiva e switch sono sul layer F.Fab. I riferimenti
  dei LED dati sono su F.Fab, lasciando soltanto D7…D0 visibili sul fronte.
- Lo spazio per i corpi dei connettori è riferito agli header non schermati
  della BOM; verificare l'ingombro dei terminali del cavo scelti per il case.

Usare solo lo ZIP Gerber di questa consegna: gli export precedenti della
revisione B non rappresentano queste dimensioni.

Questa consegna sostituisce anche il precedente layout slim senza SW1.
Il manifest identifica `2026-10-07-slim-led-switch`: usare gli ZIP rigenerati
insieme allo schema e alla BOM di questa versione. Le dimensioni esterne
e i fori di montaggio restano quelli del layout slim.

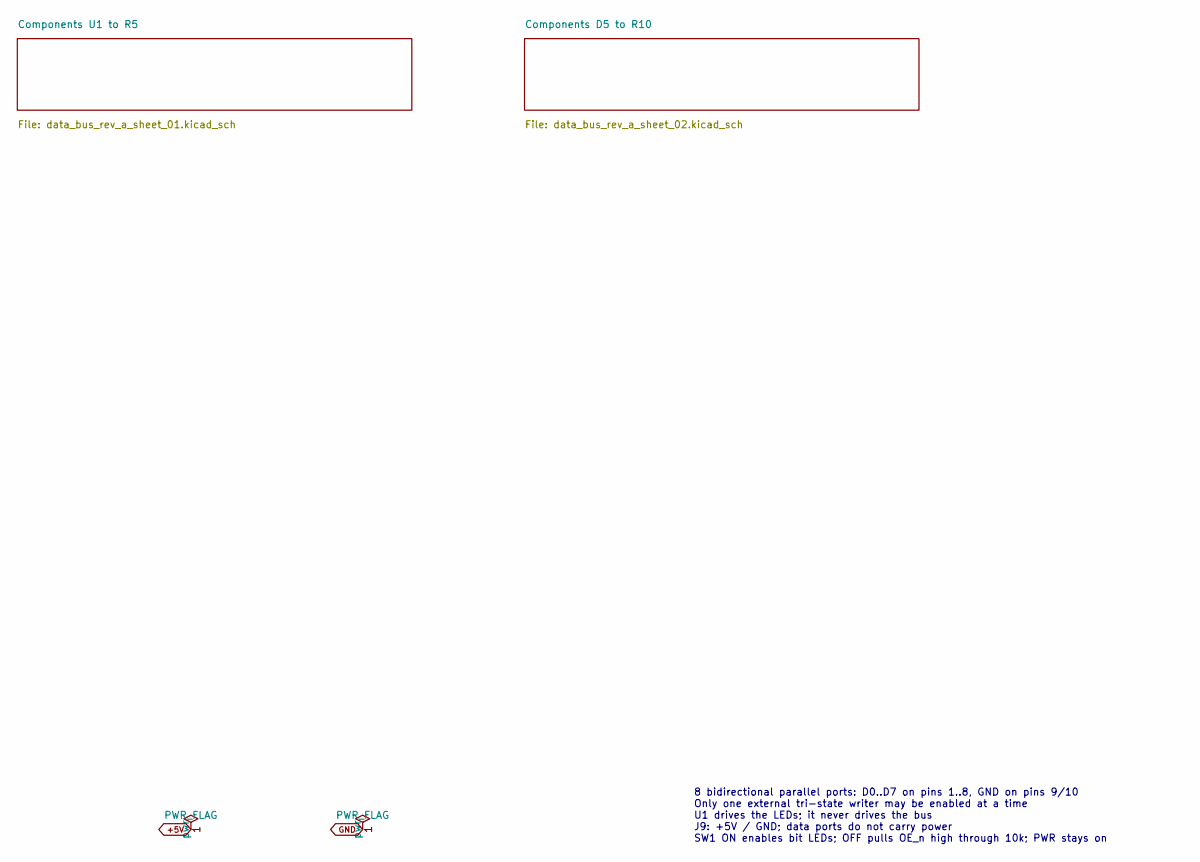
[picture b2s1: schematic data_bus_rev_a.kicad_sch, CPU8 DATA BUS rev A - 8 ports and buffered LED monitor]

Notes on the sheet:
8 bidirectional parallel ports: D0..D7 on pins 1..8, GND on pins 9/10 Only one external tri-state writer may be enabled at a time U1 drives the LEDs; it never drives the bus J9: +5V / GND; data ports do not carry power SW1 ON enables bit LEDs; OFF pulls OE_n high through 10k; PWR stays on
